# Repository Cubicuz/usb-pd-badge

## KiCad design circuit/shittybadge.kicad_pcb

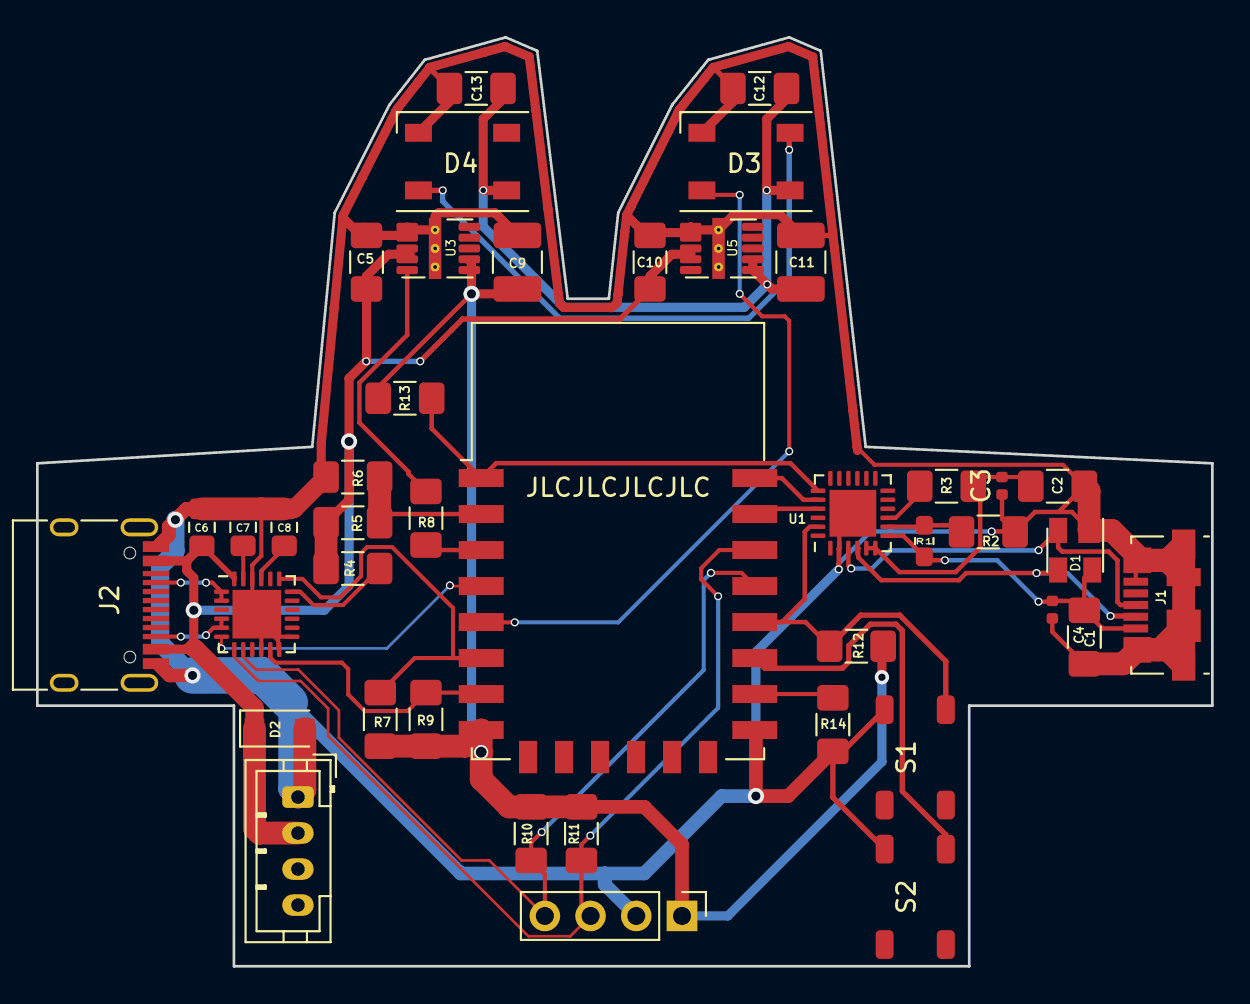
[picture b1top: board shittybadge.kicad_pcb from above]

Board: 2 copper layers, 65.3 x 51.6 mm, 42 parts (0 on the bottom side), 31 nets.

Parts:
C1, C2: 4,7u; C_1206_3216Metric_Pad1.42x1.75mm_HandSolder
C3, C4: 0,1u; C_0402_1005Metric
C5, C10, C12, C13: 10u; C_1206_3216Metric_Pad1.42x1.75mm_HandSolder
C6, C7, C8: 1u; C_0805_2012Metric_Pad1.15x1.40mm_HandSolder
C9, C11: 47u; C_1210_3225Metric_Pad1.42x2.65mm_HandSolder
D1: SP0503BAHT; SOT-143
D2: D; D_SOD-123F
D3, D4: SK6812; LED_SK6812_PLCC4_5.0x5.0mm_P3.2mm
J1: USB_B_Micro; USB_Micro-B_Molex_47346-0001
J2: E8124-015-01; USB_C_Receptacle_HRO_TYPE-C-31-M-12
J4: B4B-PH-K-S_LF__SN_; JST_PH_B4B-PH-K_1x04_P2.00mm_Vertical
R1: 22.1k; R_0603_1608Metric_Pad1.05x0.95mm_HandSolder
R2, R5: 47.5k; R_1206_3216Metric_Pad1.42x1.75mm_HandSolder
R3, R4: 1k; R_1206_3216Metric_Pad1.42x1.75mm_HandSolder
R6: 2.5k; R_1206_3216Metric_Pad1.42x1.75mm_HandSolder
R7, R8, R9, R10, R11, R12, R13, R14: 10k; R_1206_3216Metric_Pad1.42x1.75mm_HandSolder
S1, S2: pts647
U1: CP2102N-A01-GQFN24; QFN-24-1EP_4x4mm_P0.5mm_EP2.6x2.6mm
U2: STUSB4500QTR; QFN-24-1EP_4x4mm_P0.5mm_EP2.7x2.7mm
U3: LMZM23601V3; Texas_SIL0010A_MicroSiP-10-1EP_3.8x3mm_P0.6mm_EP0.7x2.9mm_T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
U4: ESP-12E
U5: LMZM23601V5; Texas_SIL0010A_MicroSiP-10-1EP_3.8x3mm_P0.6mm_EP0.7x2.9mm_T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
U6: myDisplay; myI2CDisplay

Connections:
+3V3: C9.1, R7.2, R9.2, R10.2, R11.2, R12.1, R13.2, U3.6, U3.7, U4.8, U6.1
+5V: C11.1, C12.1, C13.1, D3.3, D4.3, U5.6, U5.7
ALERT_PD: R7.1, U2.19, U4.6
ATTACH_PD: R9.1, U2.11, U4.7
GND: C1.1, C2.2, C3.1, C4.2, C5.2, C6.2, C7.1, C8.1, C9.2, C10.2, C11.2, C12.2, C13.2, D1.1, D2.2, D3.1, D4.1, J1.5, J1.6, J2.A1, J2.A12, J2.B1, J2.B12, J4.1, R2.2, R6.2, R14.2, S1.3, S2.3, U1.2, U1.25, U2.10, U2.12, U2.13, U2.22, U2.25, U3.1, U3.2, U3.11, U4.15, U5.1, U5.2, U5.11, U6.2
unnamed: C1.2, C4.1, D1.4, J1.1, R1.2, U1.7
unnamed: C2.1, C3.2, R3.1, U1.5, U1.6
unnamed: C7.2, U2.23
unnamed: C8.2, U2.21
unnamed: D1.2, J1.3, U1.3
unnamed: D1.3, J1.2, U1.4
unnamed: D3.2, U4.5
unnamed: D3.4, D4.2
unnamed: J2.A5, U2.1, U2.2
unnamed: J2.B5, U2.4, U2.5
unnamed: R1.1, R2.1, U1.8
unnamed: R3.2, U1.9
unnamed: R4.1, U2.18
unnamed: R5.2, R6.1, U4.2
unnamed: R8.1, U4.3
unnamed: R8.2, U3.5
unnamed: R12.2, S1.1, U1.23, U4.18
unnamed: R13.1, U1.19, U4.1
unnamed: R14.1, U4.16
unnamed: S2.1, U4.17
unnamed: U1.20, U4.22
unnamed: U1.21, U4.21
RST_PD: U2.6, U4.4
SCL: R11.1, U2.7, U4.20, U6.3
SDA: R10.1, U2.8, U4.19, U6.4
VBUS: C5.1, C6.1, C10.1, D2.1, J2.A4, J2.A9, J2.B4, J2.B9, J4.2, R4.2, R5.1, U2.24, U3.3, U3.4, U5.3, U5.4

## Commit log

2020-09-17 [add] gitignore
2020-09-17 [add] kicad files
2020-09-21 warenkorb 4 backup reasons
2020-10-01 update display
2020-10-01 start routing
2020-10-02 changed usbc to usb2
2020-10-15 did some routing
2020-10-16 continued routing
2020-10-18 done routing v1
2020-11-08 ordering
